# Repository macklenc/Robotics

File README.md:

Robotics
========
Welcome to the University of Colorado at Colorado Springs Institute of Electrical and Electronics Engineers Robotics Team resource repository.

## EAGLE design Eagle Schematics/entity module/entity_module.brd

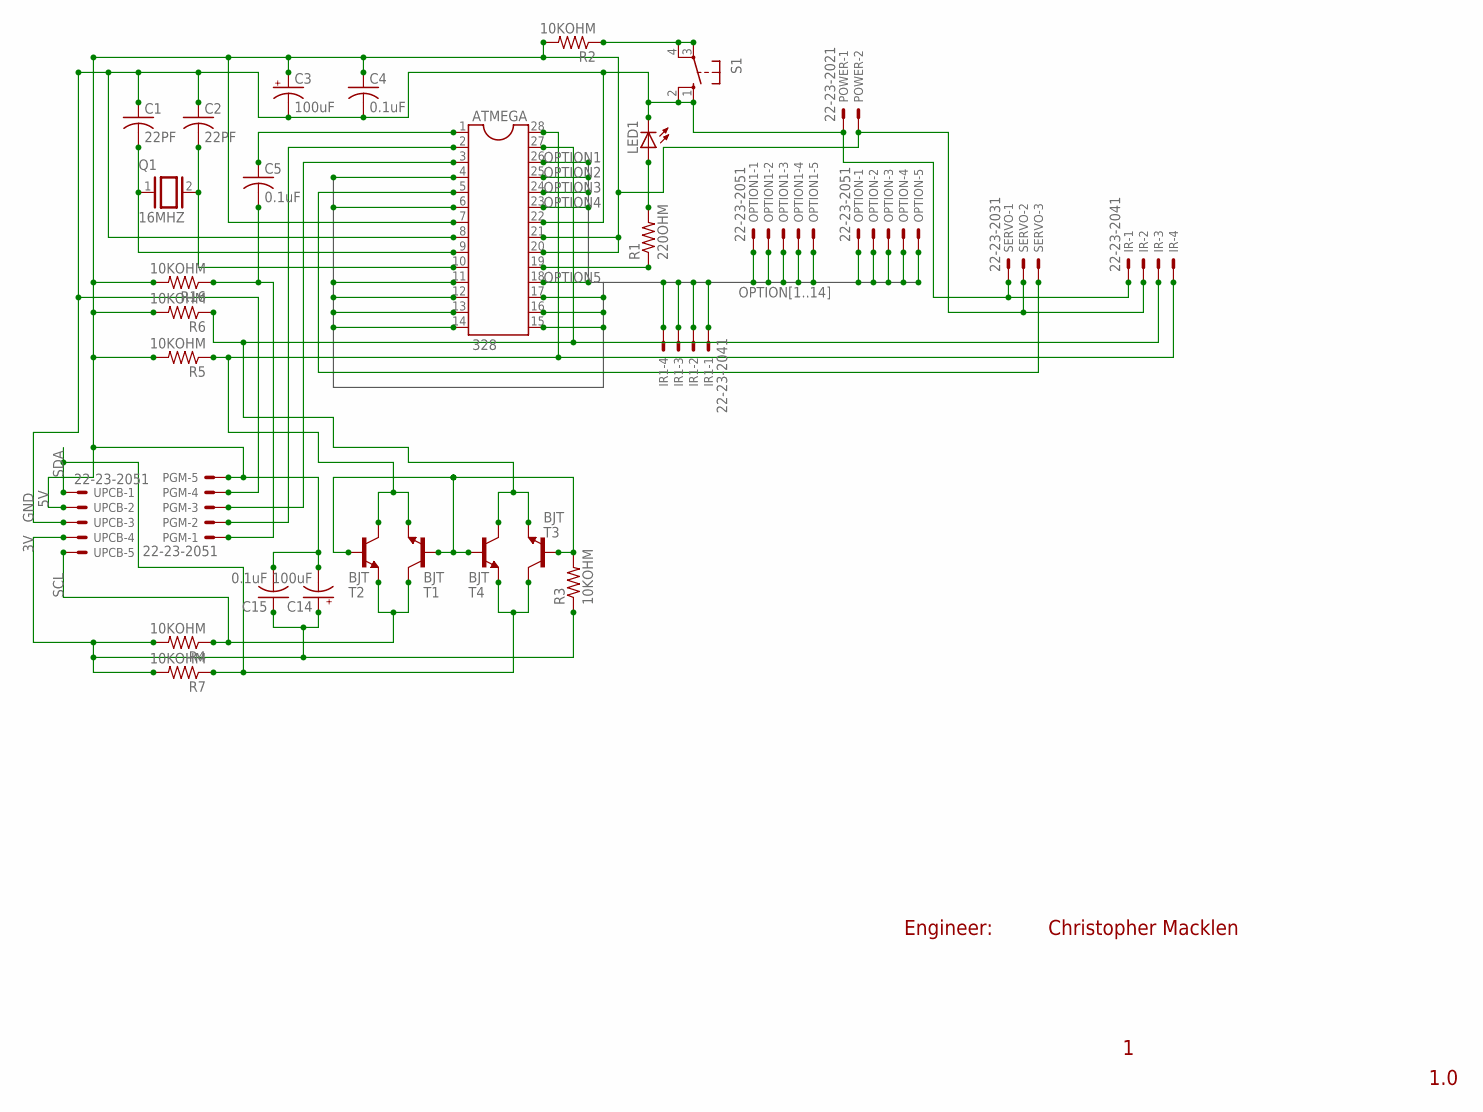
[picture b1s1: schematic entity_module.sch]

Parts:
ATMEGA: 328; DIL28-6
C1, C2: 22PF; C025-024X044
C3, C14: 100uF; E2-5
C4, C5, C15: 0.1uF; C025-024X044
IR: 22-23-2041
IR1: 22-23-2041; MPN 22-23-2041
LED1: LED3MM
OPTION: 22-23-2051
OPTION1: 22-23-2051; MPN 22-23-2051
PGM: 22-23-2051
POWER: 22-23-2021
Q1: 16MHZ; QS
R1: 220OHM; 0204/7
R2, R3, R4, R5, R6, R7, R16: 10KOHM; 0204/7
S1: 10-XX; B3F-10XX
SERVO: 22-23-2031
T1, T2, T3, T4: BJT; TO92-E1
UPCB: 22-23-2051

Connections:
3V: C14.+, C15.1, R3.1, R4.2, R7.2, UPCB.4
5V: ATMEGA.7, ATMEGA.20, ATMEGA.21, C3.+, C4.1, C14.-, C15.2, IR.2, PGM.5, POWER.2, R2.2, R5.2, R6.2, R16.2, SERVO.2, UPCB.2
CLK-1: ATMEGA.9, C1.2, Q1.1
CLK-2: ATMEGA.10, C2.2, Q1.2
GND: ATMEGA.8, ATMEGA.22, C1.1, C2.1, C3.-, C4.2, IR.1, LED1.K (C), PGM.4, POWER.1, S1.1 (S), S1.2 (S1), SERVO.1, UPCB.3
I2C-EN: R3.2, T1.2 (B), T2.2 (B), T3.2 (B), T4.2 (B)
LEDNET-1: ATMEGA.19, R1.1
LEDNET-2: LED1.A, R1.2
unnamed: ATMEGA.5, SERVO.3
OPTION1: ATMEGA.26, OPTION.1
OPTION2: ATMEGA.25, OPTION.2
OPTION3: ATMEGA.24, OPTION.3
OPTION4: ATMEGA.23, OPTION.4
OPTION5: ATMEGA.18, OPTION.5
OPTION6: ATMEGA.4, OPTION1.1
OPTION7: ATMEGA.6, OPTION1.2
OPTION8: ATMEGA.11, OPTION1.3
OPTION9: ATMEGA.12, OPTION1.4
OPTION10: ATMEGA.13, OPTION1.5
OPTION11: ATMEGA.14, IR1.1
OPTION12: ATMEGA.15, IR1.2
OPTION13: ATMEGA.16, IR1.3
OPTION14: ATMEGA.17, IR1.4
RST-1: C5.2, PGM.1, R16.1
RST-2: ATMEGA.1, C5.1
RST-SW: R2.1, S1.3, S1.4 (P1)
RX-TX: ATMEGA.3, PGM.3
SCL: R4.1, T1.1 (C), T2.3 (E), UPCB.5
SCL-5V: ATMEGA.28, IR.4, R5.1, T1.3 (E), T2.1 (C)
SDA: R7.1, T3.1 (C), T4.3 (E), UPCB.1
SDA-5V: ATMEGA.27, IR.3, R6.1, T3.3 (E), T4.1 (C)
TX-RX: ATMEGA.2, PGM.2

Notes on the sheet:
Christopher Macklen
1.0
Engineer:

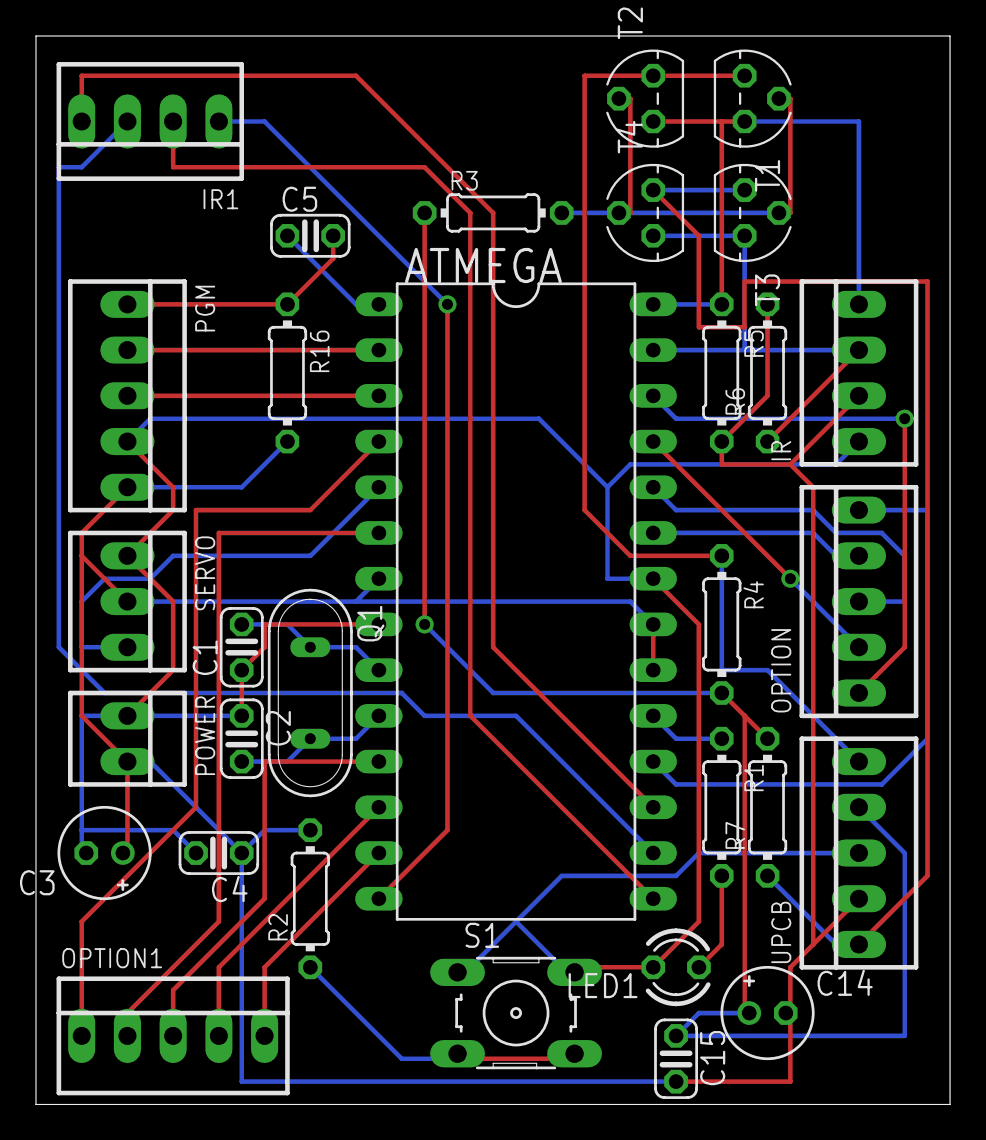
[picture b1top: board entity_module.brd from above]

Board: 2 copper layers, 50.8 x 59.4 mm, 31 parts (0 on the bottom side), 32 nets.

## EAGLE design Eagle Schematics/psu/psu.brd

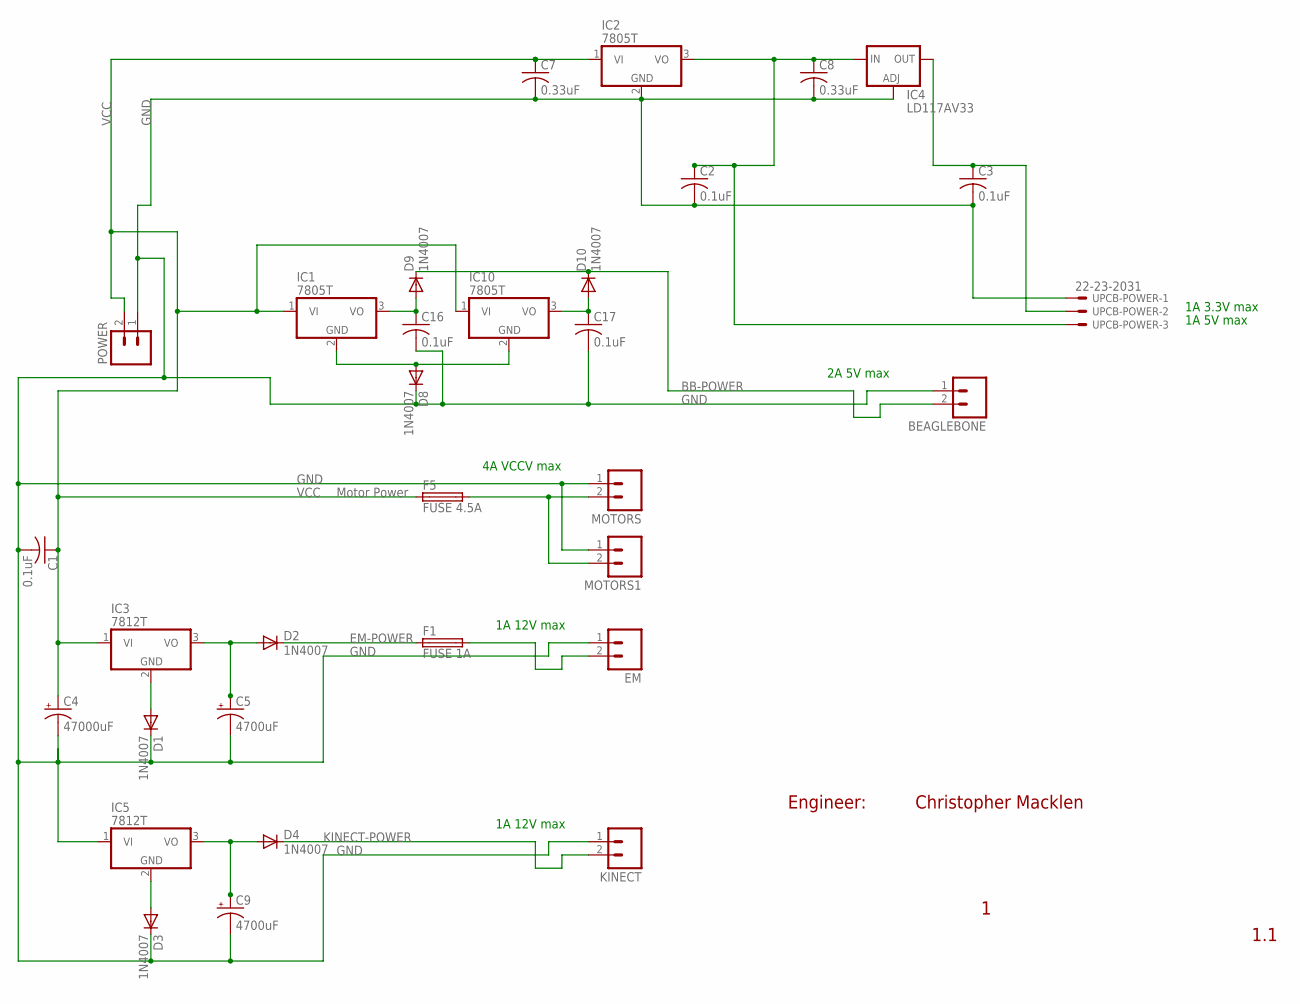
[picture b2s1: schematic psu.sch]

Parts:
BEAGLEBONE: M02; 02P
C1, C2, C3, C16, C17: 0.1uF; C025-025X050
C4: 47000uF; E2,5-6E
C5, C9: 4700uF; E2,5-6E
C7, C8: 0.33uF; C025-025X050
D1, D2, D3, D4, D8, D9, D10: 1N4007; DO41-10
EM: M02; 02P
F1: FUSE 1A; PICOFUSE
F5: FUSE 4.5A; PICOFUSE
IC1, IC2, IC10: 7805T; TO220H
IC3, IC5: 7812T; TO220H
IC4: LD117AV33; TO220L1
KINECT: M02; 02P
MOTORS, MOTORS1: M02; 02P
POWER: M02; 02P
UPCB-POWER: 22-23-2031

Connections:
3.3V: C3.1, IC4.2 (OUT), UPCB-POWER.2
5-1A,1: C16.1, D9.A, IC1.3 (VO)
5V: C2.1, C8.1, IC2.3 (VO), IC4.3 (IN), UPCB-POWER.3
5V-1A,2: C17.1, D10.A, IC10.3 (VO)
12V: C5.+, D2.A, IC3.3 (VO)
12V1: C9.+, D4.A, IC5.3 (VO)
BB-POWER: BEAGLEBONE.2, D9.C, D10.C
EM-POWER: D2.C, F1.1
GND: BEAGLEBONE.1, C1.2, C2.2, C3.2, C4.-, C5.-, C7.2, C8.2, C9.-, C16.2, C17.2, D1.C, D3.C, D8.C, EM.1, IC2.2 (GND), IC4.1 (ADJ), KINECT.1, MOTORS.1, MOTORS1.1, POWER.1, UPCB-POWER.1
GND-IC1: D3.A, IC5.2 (GND)
GND-IC1,10: D8.A, IC1.2 (GND), IC10.2 (GND)
GND-IC3: D1.A, IC3.2 (GND)
KINECT-POWER: D4.C, KINECT.2
unnamed: F5.2, MOTORS.2, MOTORS1.2
unnamed: EM.2, F1.2
VCC: C1.1, C4.+, C7.1, F5.1, IC1.1 (VI), IC2.1 (VI), IC3.1 (VI), IC10.1 (VI), POWER.2
VCC1: IC5.1 (VI)

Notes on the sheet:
Christopher Macklen
1.1
Engineer:
2A 5V max
1A 12V max
1A 5V max
1A 3.3V max
Motor Power
4A VCCV max

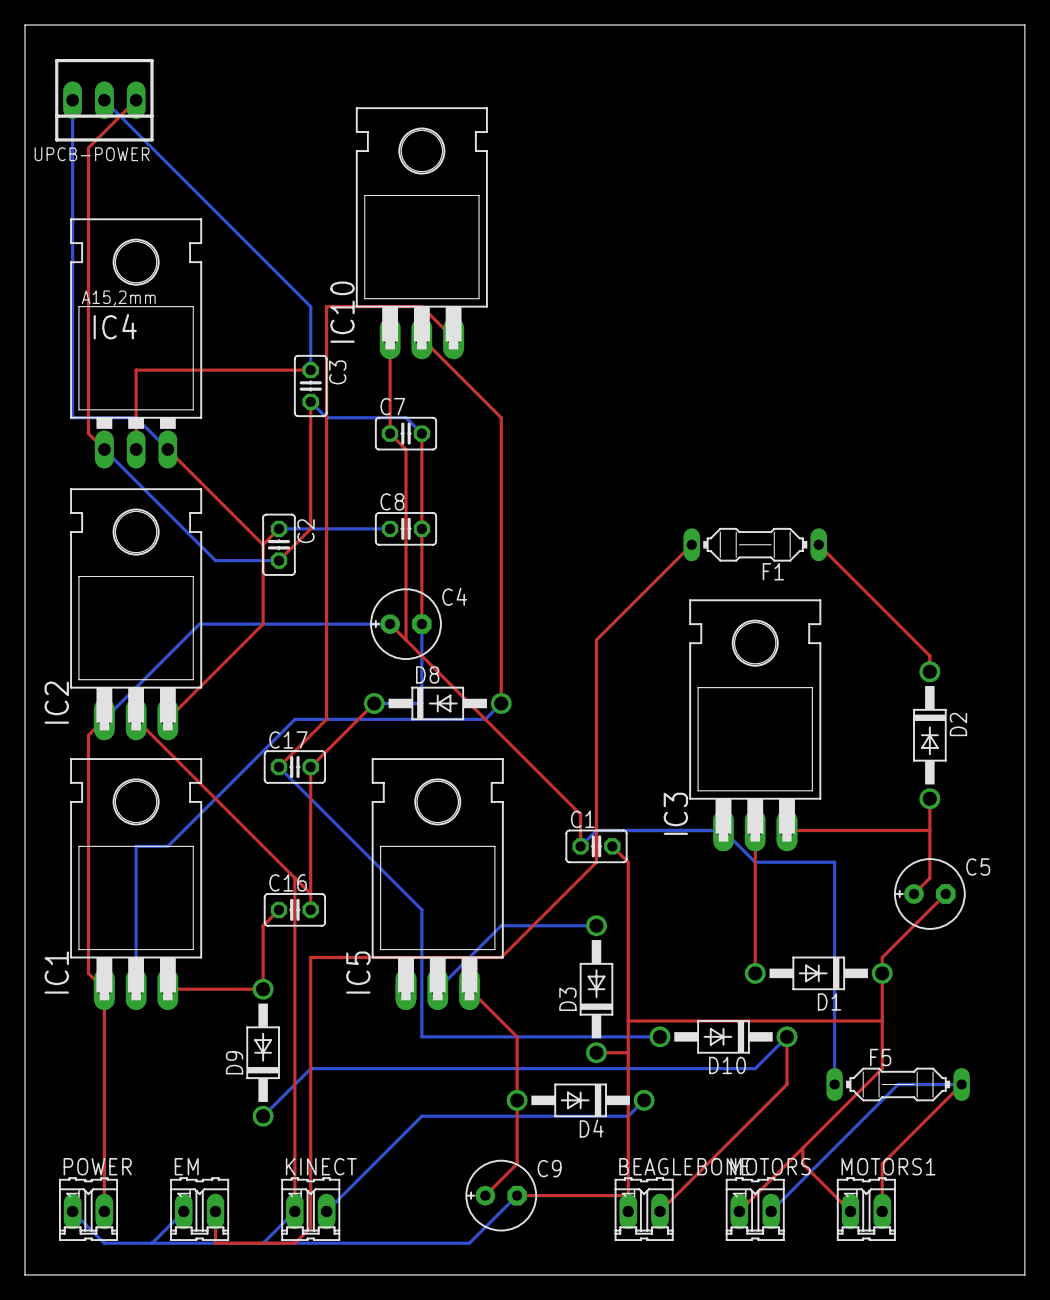
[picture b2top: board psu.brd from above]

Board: 2 copper layers, 80.0 x 100.0 mm, 32 parts (0 on the bottom side), 16 nets.

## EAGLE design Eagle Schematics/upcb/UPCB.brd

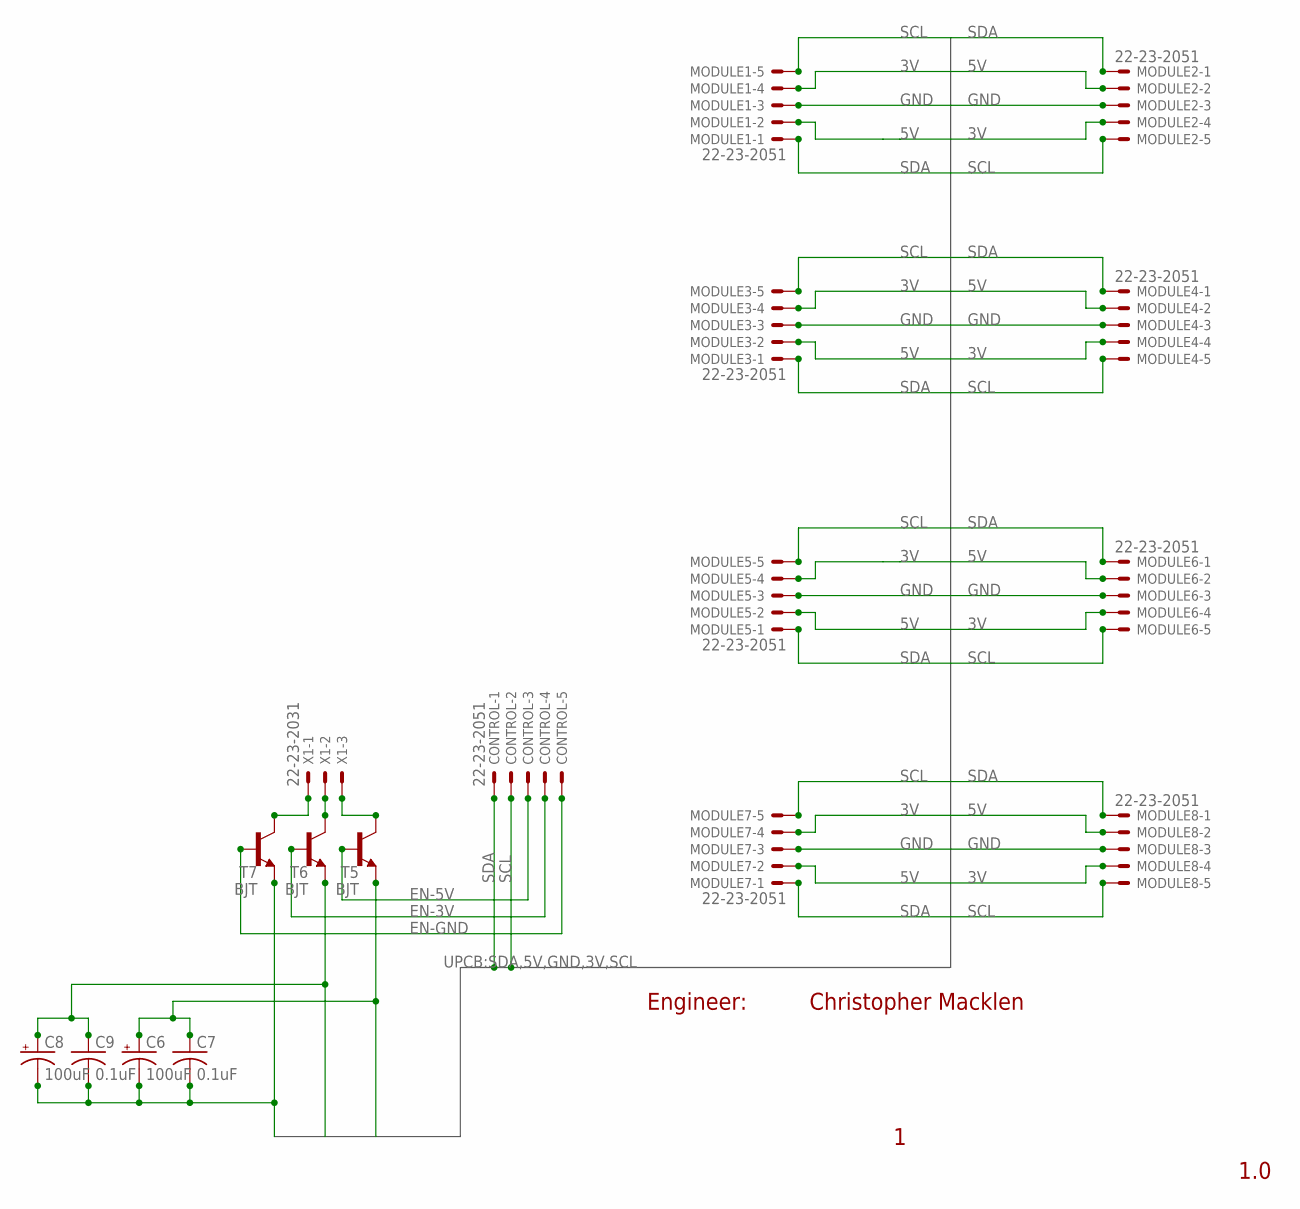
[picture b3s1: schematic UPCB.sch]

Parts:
C6, C8: 100uF; E2-5
C7, C9: 0.1uF; C025-024X044
CONTROL: 22-23-2051
MODULE1, MODULE2, MODULE3, MODULE4, MODULE5, MODULE6, MODULE7, MODULE8: 22-23-2051
T5, T6, T7: BJT; TO92-E1
X1: 22-23-2031

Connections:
3V: C8.+, C9.1, MODULE1.4, MODULE2.4, MODULE3.4, MODULE4.4, MODULE5.4, MODULE6.4, MODULE7.4, MODULE8.4, T6.3 (E)
5V: C6.+, C7.1, MODULE1.2, MODULE2.2, MODULE3.2, MODULE4.2, MODULE5.2, MODULE6.2, MODULE7.2, MODULE8.2, T5.3 (E)
EN-3V: CONTROL.4, T6.2 (B)
EN-5V: CONTROL.3, T5.2 (B)
EN-GND: CONTROL.5, T7.2 (B)
GND: C6.-, C7.2, C8.-, C9.2, MODULE1.3, MODULE2.3, MODULE3.3, MODULE4.3, MODULE5.3, MODULE6.3, MODULE7.3, MODULE8.3, T7.3 (E)
SCL: CONTROL.2, MODULE1.5, MODULE2.5, MODULE3.5, MODULE4.5, MODULE5.5, MODULE6.5, MODULE7.5, MODULE8.5
SDA: CONTROL.1, MODULE1.1, MODULE2.1, MODULE3.1, MODULE4.1, MODULE5.1, MODULE6.1, MODULE7.1, MODULE8.1
UF-3V: T6.1 (C), X1.2
UF-5V: T5.1 (C), X1.3
UF-GND: T7.1 (C), X1.1

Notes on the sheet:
Christopher Macklen
1.0
Engineer:

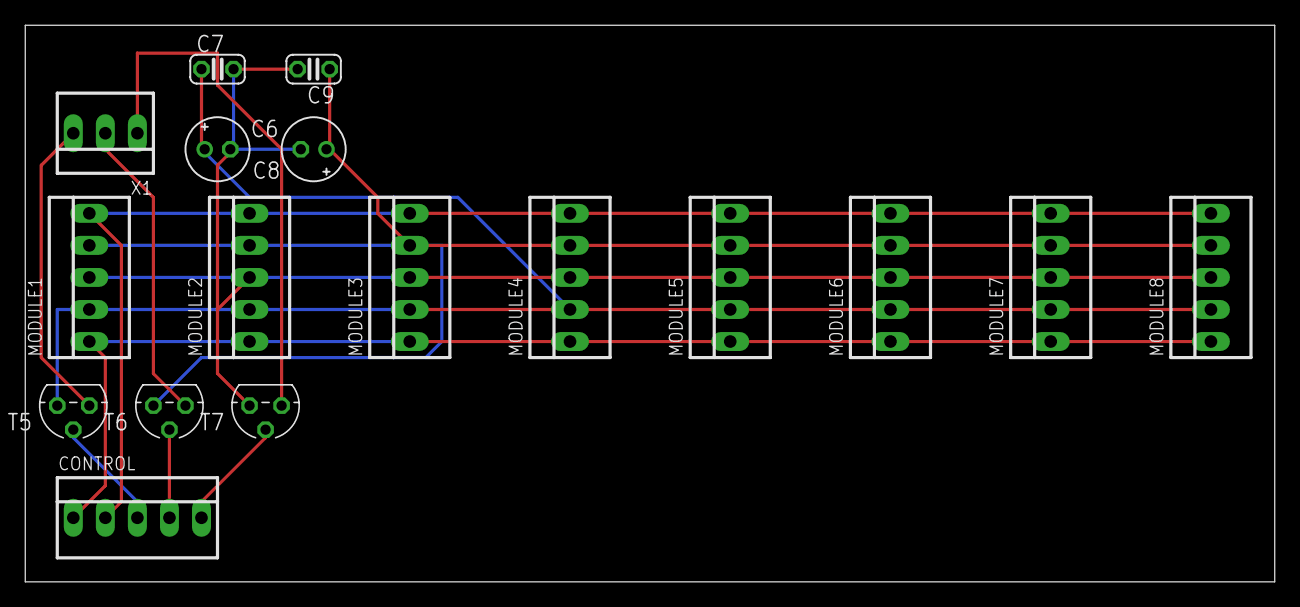
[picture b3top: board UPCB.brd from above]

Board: 2 copper layers, 99.0 x 44.1 mm, 17 parts (0 on the bottom side), 11 nets.

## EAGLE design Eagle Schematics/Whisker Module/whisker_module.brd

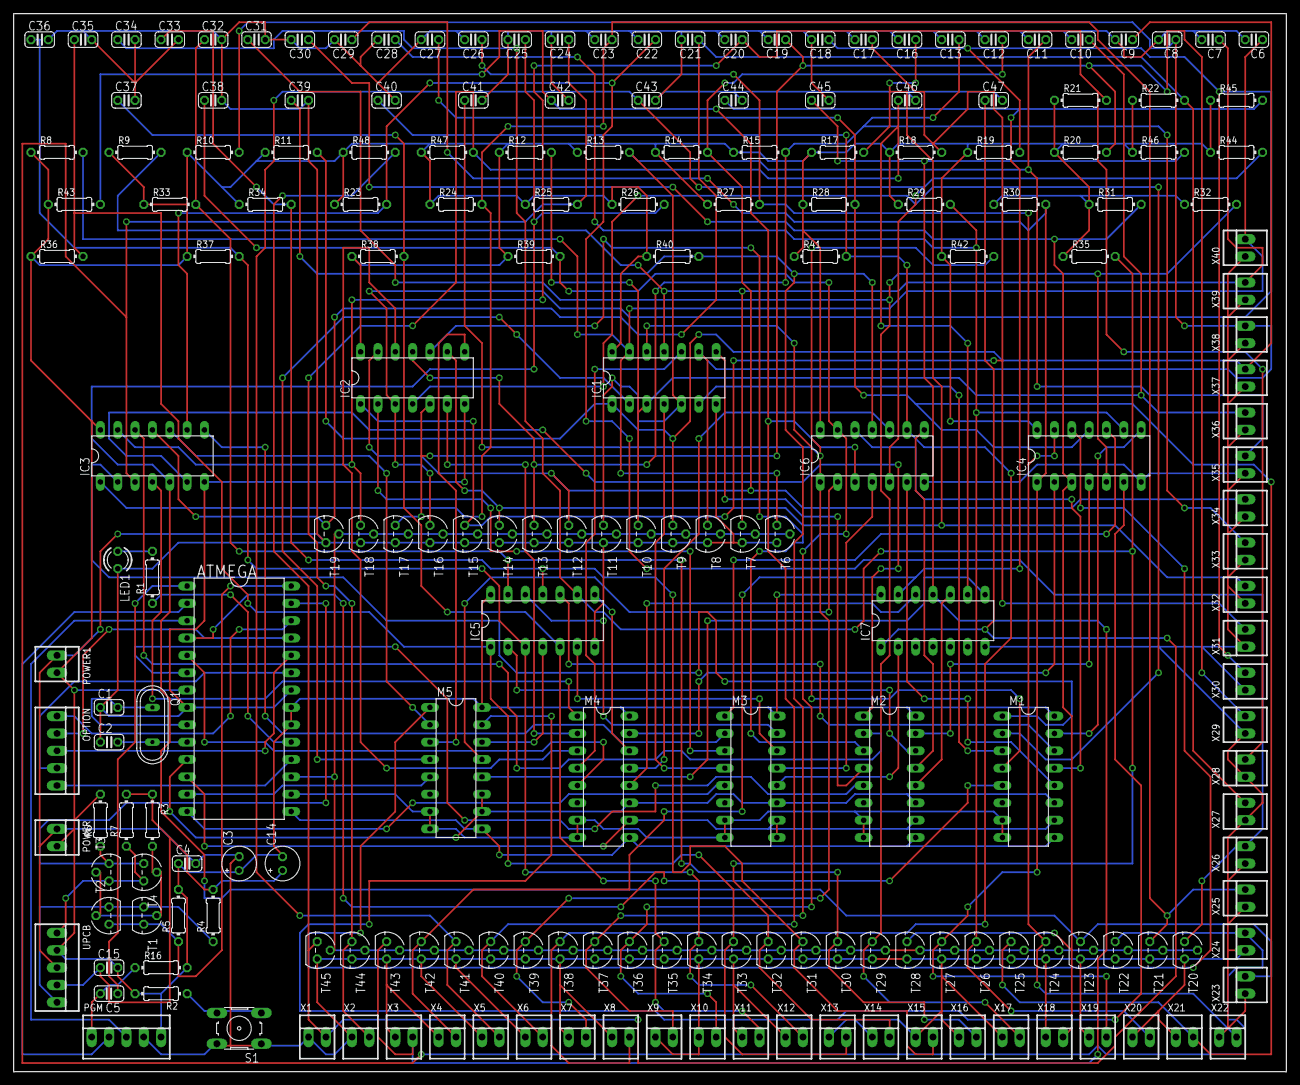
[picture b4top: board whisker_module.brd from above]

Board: 2 copper layers, 186.4 x 154.9 mm, 200 parts (0 on the bottom side), 112 nets.

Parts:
ATMEGA: 328; DIL28-6
C1, C2: 22PF; C025-024X044
C3, C14: 100uF; E2-5
C4, C5, C6, C7, C8, C9, C10, C11, C12, C13, C15, C16, C17, C18, C19, C20, C21, C22, C23, C24, C25, C26, C27, C28, C29, C30, C31, C32, C33, C34, C35, C36, C37, C38, C39, C40, C41, C42, C43, C44, C45, C46, C47: 0.1uF; C025-024X044
IC1, IC2, IC3, IC4, IC5, IC6, IC7: 74LS14N; DIL14
LED1: LED3MM
M1, M2, M3, M4, M5: CD74HCT151E
OPTION: 22-23-2051
PGM: 22-23-2051
POWER, POWER1: 22-23-2021
Q1: 16MHZ; QS
R1: 220OHM; 0204/7
R2, R3, R4, R5, R6, R7, R8, R9, R10, R11, R12, R13, R14, R15, R16, R17, R18, R19, R20, R21, R22, R23, R24, R25, R26, R27, R28, R29, R30, R31, R32, R33, R34, R35, R36, R37, R38, R39, R40, R41, R42, R43, R44, R45, R46, R47, R48: 10KOHM; 0204/7
S1: B3F-10XX
T1, T2, T3, T4: BJT; TO92-E1
T6, T7, T8, T9, T10, T11, T12, T13, T14, T15, T16, T17, T18, T19, T20, T21, T22, T23, T24, T25, T26, T27, T28, T29, T30, T31, T32, T33, T34, T35, T36, T37, T38, T39, T40, T41, T42, T43, T44, T45: 2N3565; TO92
UPCB: 22-23-2051
X1, X2, X3, X4, X5, X6, X7, X8, X9, X10, X11, X12, X13, X14, X15, X16, X17, X18, X19, X20, X21, X22, X23, X24, X25, X26, X27, X28, X29, X30, X31, X32, X33, X34, X35, X36, X37, X38, X39, X40: 22-23-2021

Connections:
3V: C14.+, C15.1, R3.1, R4.2, R7.2, UPCB.4
5V: ATMEGA.7, ATMEGA.20, ATMEGA.21, C3.+, C4.1, C14.-, C15.2, IC1.14, IC2.14, IC3.14, IC4.14, IC5.14, IC6.14, IC7.14, M1.16, M2.16, M3.16, M4.16, M5.16, PGM.5, POWER.2, POWER1.2, R2.2, R5.2, R6.2, R8.1, R9.1, R10.1, R11.1, R12.1, R13.1, R14.1, R15.1, R16.2, R17.1, R18.1, R19.1, R20.1, R21.1, R22.1, R23.1, R24.1, R25.1, R26.1, R27.1, R28.1, R29.1, R30.1, R31.1, R32.1, R33.1, R34.1, R35.1, R36.1, R37.1, R38.1, R39.1, R40.1, R41.1, R42.1, R43.1, R44.1, R45.1, R46.1, R47.1, R48.1, UPCB.2
CLK-1: ATMEGA.9, C1.2, Q1.1
CLK-2: ATMEGA.10, C2.2, Q1.2
D1: IC1.12, M1.4
D2: IC1.10, M4.4
D3: IC1.8, M2.4
D4: IC1.2, M5.4
D5: IC1.4, M3.4
D6: IC1.6, M1.3
D7: IC2.12, M4.3
D8: IC2.10, M2.3
D9: IC2.8, M5.3
D10: IC2.2, M3.3
D11: IC2.4, M1.2
D12: IC2.6, M4.2
D13: IC3.12, M2.2
D14: IC3.10, M5.2
D15: IC3.8, M3.2
D16: IC3.2, M1.1
D17: IC3.4, M4.1
D18: IC3.6, M2.1
D19: IC4.12, M5.1
D20: IC4.10, M3.1
D21: IC4.8, M1.15
D22: IC4.2, M4.15
D23: IC4.4, M2.15
D24: IC4.6, M5.15
D25: IC5.12, M3.15
D26: IC5.10, M1.14
D27: IC5.8, M4.14
D28: IC5.2, M2.14
D29: IC5.4, M5.14
D30: IC5.6, M3.14
D31: IC6.12, M1.13
D32: IC6.10, M4.13
D33: IC6.8, M2.13
D34: IC6.2, M5.13
D35: IC6.4, M3.13
D36: IC6.6, M1.12
D37: IC7.12, M4.12
D38: IC7.10, M2.12
D39: IC7.8, M5.12
D40: IC7.2, M3.12
GND: ATMEGA.8, ATMEGA.22, C1.1, C2.1, C3.-, C4.2, C6.2, C7.2, C8.2, C9.2, C10.2, C11.2, C12.2, C13.2, C16.2, C17.2, C18.2, C19.2, C20.2, C21.2, C22.2, C23.2, C24.2, C25.2, C26.2, C27.2, C28.2, C29.2, C30.2, C31.2, C32.2, C33.2, C34.2, C35.2, C36.2, C37.2, C38.2, C39.2, C40.2, C41.2, C42.2, C43.2, C44.2, C45.2, C46.2, C47.2, IC1.7, IC2.7, IC3.7, IC4.7, IC5.7, IC6.7, IC7.7, LED1.K, PGM.4, POWER.1, POWER1.1, S1.1, S1.2, T6.1, T7.1, T8.1, T9.1, T10.1, T11.1, T12.1, T13.1, T14.1, T15.1, T16.1, T17.1, T18.1, T19.1, T20.1, T21.1, T22.1, T23.1, T24.1, T25.1, T26.1, T27.1, T28.1, T29.1, T30.1, T31.1, T32.1, T33.1, T34.1, T35.1, T36.1, T37.1, T38.1, T39.1, T40.1, T41.1, T42.1, T43.1, T44.1, T45.1, UPCB.3, X1.1, X2.1, X3.1, X4.1, X5.1, X6.1, X7.1, X8.1, X9.1, X10.1, X11.1, X12.1, X13.1, X14.1, X15.1, X16.1, X17.1, X18.1, X19.1, X20.1, X21.1, X22.1, X23.1, X24.1, X25.1, X26.1, X27.1, X28.1, X29.1, X30.1, X31.1, X32.1, X33.1, X34.1, X35.1, X36.1, X37.1, X38.1, X39.1, X40.1
I2C-EN: R3.2, T1.2, T2.2, T3.2, T4.2
LEDNET-1: ATMEGA.19, R1.1
LEDNET-2: LED1.A, R1.2
OPTION1: ATMEGA.26, OPTION.1
OPTION2: ATMEGA.25, OPTION.2
OPTION3: ATMEGA.24, OPTION.3
OPTION4: ATMEGA.23, OPTION.4
OPTION5: ATMEGA.18, OPTION.5
RESULT1: ATMEGA.4, M1.5
RESULT2: ATMEGA.5, M4.5
RESULT3: ATMEGA.6, M2.5
RESULT4: ATMEGA.13, M5.5
RESULT5: ATMEGA.14, M3.5
RST-1: C5.2, PGM.1, R16.1
RST-2: ATMEGA.1, C5.1
RST-SW: R2.1, S1.3, S1.4
RX-TX: ATMEGA.3, PGM.3
SCL: R4.1, T1.1, T2.3, UPCB.5
SCL-5V: ATMEGA.28, R5.1, T1.3, T2.1
SDA: R7.1, T3.1, T4.3, UPCB.1
SDA-5V: ATMEGA.27, R6.1, T3.3, T4.1
SELECT1: ATMEGA.11, M1.11, M2.11, M3.11, M4.11, M5.10, M5.11
SELECT2: ATMEGA.12, M1.10, M2.10, M3.9, M3.10, M4.10
SELECT3: ATMEGA.15, M1.9, M2.9, M4.9, M5.9
SELECT4: ATMEGA.16, M1.7, M1.8, M2.7, M2.8, M3.7, M3.8, M4.7, M4.8, M5.7, M5.8
SELECT5: ATMEGA.17, T6.2, T7.2, T8.2, T9.2, T10.2, T11.2, T12.2, T13.2, T14.2, T15.2, T16.2, T17.2, T18.2, T19.2, T20.2, T21.2, T22.2, T23.2, T24.2, T25.2, T26.2, T27.2, T28.2, T29.2, T30.2, T31.2, T32.2, T33.2, T34.2, T35.2, T36.2, T37.2, T38.2, T39.2, T40.2, T41.2, T42.2, T43.2, T44.2, T45.2
TX-RX: ATMEGA.2, PGM.2
W1: C6.1, IC1.13, R8.2, T6.3, X40.2
W2: C7.1, IC1.11, R9.2, T7.3, X39.2
W3: C8.1, IC1.9, R10.2, T8.3, X38.2
W4: C9.1, IC1.1, R11.2, T9.3, X37.2
W5: C10.1, IC1.3, R12.2, T10.3, X36.2
W6: C11.1, IC1.5, R13.2, T11.3, X35.2
W7: C12.1, IC2.13, R14.2, T12.3, X34.2
W8: C13.1, IC2.11, R15.2, T13.3, X33.2
W9: C16.1, IC2.9, R17.2, T14.3, X32.2
W10: C17.1, IC2.1, R18.2, T15.3, X31.2
W11: C18.1, IC2.3, R19.2, T16.3, X30.2
W12: C19.1, IC2.5, R20.2, T17.3, X29.2
W13: C20.1, IC3.13, R21.2, T18.3, X28.2
W14: C21.1, IC3.11, R22.2, T19.3, X27.2
W15: C22.1, IC3.9, R23.2, T20.3, X26.2
W16: C23.1, IC3.1, R24.2, T21.3, X25.2
W17: C24.1, IC3.3, R25.2, T22.3, X24.2
W18: C25.1, IC3.5, R26.2, T23.3, X23.2
W19: C26.1, IC4.13, R27.2, T24.3, X22.2
W20: C27.1, IC4.11, R28.2, T25.3, X21.2
W21: C28.1, IC4.9, R29.2, T26.3, X20.2
W22: C29.1, IC4.1, R30.2, T27.3, X19.2
W23: C30.1, IC4.3, R31.2, T28.3, X18.2
W24: C31.1, IC4.5, R32.2, T29.3, X17.2
W25: C32.1, IC5.13, R33.2, T30.3, X16.2
W26: C33.1, IC5.11, R34.2, T31.3, X15.2
W27: C34.1, IC5.9, R35.2, T32.3, X14.2
W28: C35.1, IC5.1, R36.2, T33.3, X13.2
W29: C36.1, IC5.3, R37.2, T34.3, X12.2
W30: C37.1, IC5.5, R38.2, T35.3, X11.2
W31: C38.1, IC6.13, R39.2, T36.3, X10.2
W32: C39.1, IC6.11, R40.2, T37.3, X9.2
W33: C40.1, IC6.9, R41.2, T38.3, X8.2
W34: C41.1, IC6.1, R42.2, T39.3, X7.2
W35: C42.1, IC6.3, R43.2, T40.3, X6.2
W36: C43.1, IC6.5, R44.2, T41.3, X5.2
W37: C44.1, IC7.13, R45.2, T42.3, X4.2
W38: C45.1, IC7.11, R46.2, T43.3, X3.2
W39: C46.1, IC7.9, R47.2, T44.3, X2.2
W40: C47.1, IC7.1, R48.2, T45.3, X1.2

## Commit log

2012-10-09 Added git robotics readme
2012-10-09 Added github instruction file
2012-10-09 Added control branch
2012-10-09 Added navigation branch
2012-10-09 Added payload branch
2012-10-09 Added structure branch
2012-10-09 Team Roster Modified
2012-10-11 Modified team-name file
2012-10-11 Team Roster Updated
2012-10-11 Removed Shawn Smith from Team Roster
2012-10-11 Removed Shawn Smith from Team Roster Again.
2012-10-20 Added original track design
    Added the first track design alog with the original torque calculations.
2012-11-29 Added documentation information
2012-12-06 Added nav code
2012-12-06 Added Accelerometer object
2012-12-15 Changed file names
2012-12-15 Made code compileable
2012-12-15 Changed to unix line endings
2012-12-15 Changed dir name, added function list to UPC_base.h
2012-12-16 Added exception code
2012-12-16 Cleaned up UPC_base.h
2012-12-16 Made accelerometer compileable
2012-12-31 Added prox module v1.0 schematic
2012-12-31 Updated prox module schematic
2012-12-31 Fixed issue with level converter
2013-01-01 Revised design
2013-01-01 Modified prox design, added BOM
2013-01-01 Made final V1.4 revisions
2013-01-01 Worked on BOMs
2013-01-01 Revert "Worked on BOMs"
    This reverts commit a2125976a54354ab525f3884e5189c7120c6e01c.
2013-01-01 Revert "Revert "Worked on BOMs""
    This reverts commit 5e8def40d806edfa2d7bb324aa1a0e359af96b65.
2013-01-02 Created Whisker module
2013-01-02 Finished V1.0 whisker module
2013-01-02 Finished both whisker modules
2013-01-02 Modified all schematics
    Added a self debugging system.
2013-01-03 Revised designs to include self diagnostics
2013-01-03 Created UPCB and PSU schematics, finalized BOM's
2013-01-03 Renamed files
2013-01-04 Added PSU and entity module schematic
2013-01-04 Removed unused folder
2013-01-05 Added PSU BOM
2013-01-05 Updated PSU schematic and documentation
2013-01-05 Added system BOMs
2013-01-05 Finalized PSU schematic
2013-01-05 Added datasheets, finalized final_BOM
2013-01-05 Edited final BOM
2013-01-07 Minor edits
2013-01-14 Update Navigation_team.txt
    I couldn't actually find an instructions file of any sort...
